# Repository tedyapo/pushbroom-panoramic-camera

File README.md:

# pushbroom-panoramic-camera
Experimental lowres landscape camera

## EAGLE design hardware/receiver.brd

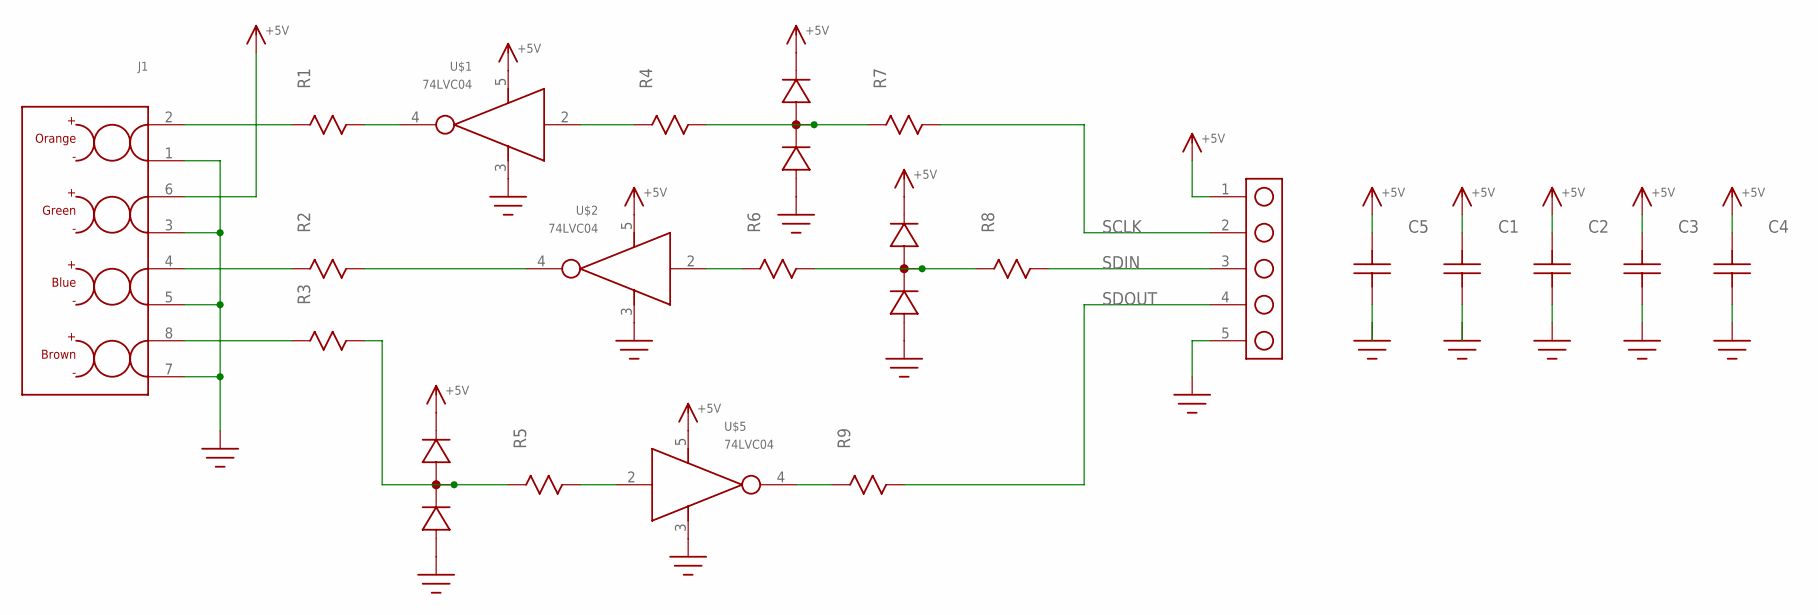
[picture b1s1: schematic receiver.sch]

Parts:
C1, C5: C1206; 1206
C2, C3, C4: C0805; 0805
J1: RJ45; RJ45_KEYSTONE_949
J2: HEADER_5PIN
R1, R2, R3, R4, R5, R6, R7, R8, R9: R0805
U$1, U$2, U$5: 74LVC04; SOT23-5
U$12, U$13, U$14: MMBD7000L; SOT-23

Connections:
+5V: C1.P$2, C2.P$2, C3.P$2, C4.P$2, C5.P$2, J1.6, J2.1, U$1.5 (VCC), U$2.5 (VCC), U$5.5 (VCC), U$12.2 (CATHODE), U$13.2 (CATHODE), U$14.2 (CATHODE)
GND: C1.P$1, C2.P$1, C3.P$1, C4.P$1, C5.P$1, J1.1, J1.3, J1.5, J1.7, J2.5, U$1.3 (GND), U$2.3 (GND), U$5.3 (GND), U$12.1 (ANODE), U$13.1 (ANODE), U$14.1 (ANODE)
unnamed: J1.2, R1.P$1
unnamed: R1.P$2, U$1.4 (OUT)
unnamed: J1.4, R2.P$1
unnamed: R2.P$2, U$2.4 (OUT)
unnamed: J1.8, R3.P$1
unnamed: R3.P$2, R5.P$1, U$14.3 (COMMON)
unnamed: R5.P$2, U$5.2 (IN)
unnamed: R6.P$1, U$2.2 (IN)
unnamed: R4.P$1, U$1.2 (IN)
unnamed: R4.P$2, R7.P$1, U$12.3 (COMMON)
unnamed: R6.P$2, R8.P$1, U$13.3 (COMMON)
unnamed: R9.P$1, U$5.4 (OUT)
SCLK: J2.2, R7.P$2
SDIN: J2.3, R8.P$2
SDOUT: J2.4, R9.P$2

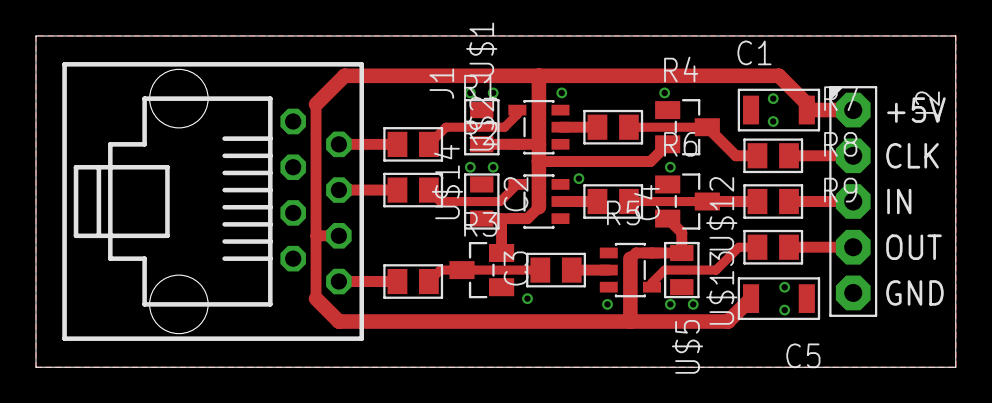
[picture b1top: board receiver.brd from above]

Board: 2 copper layers, 51.1 x 18.4 mm, 22 parts (0 on the bottom side), 17 nets.

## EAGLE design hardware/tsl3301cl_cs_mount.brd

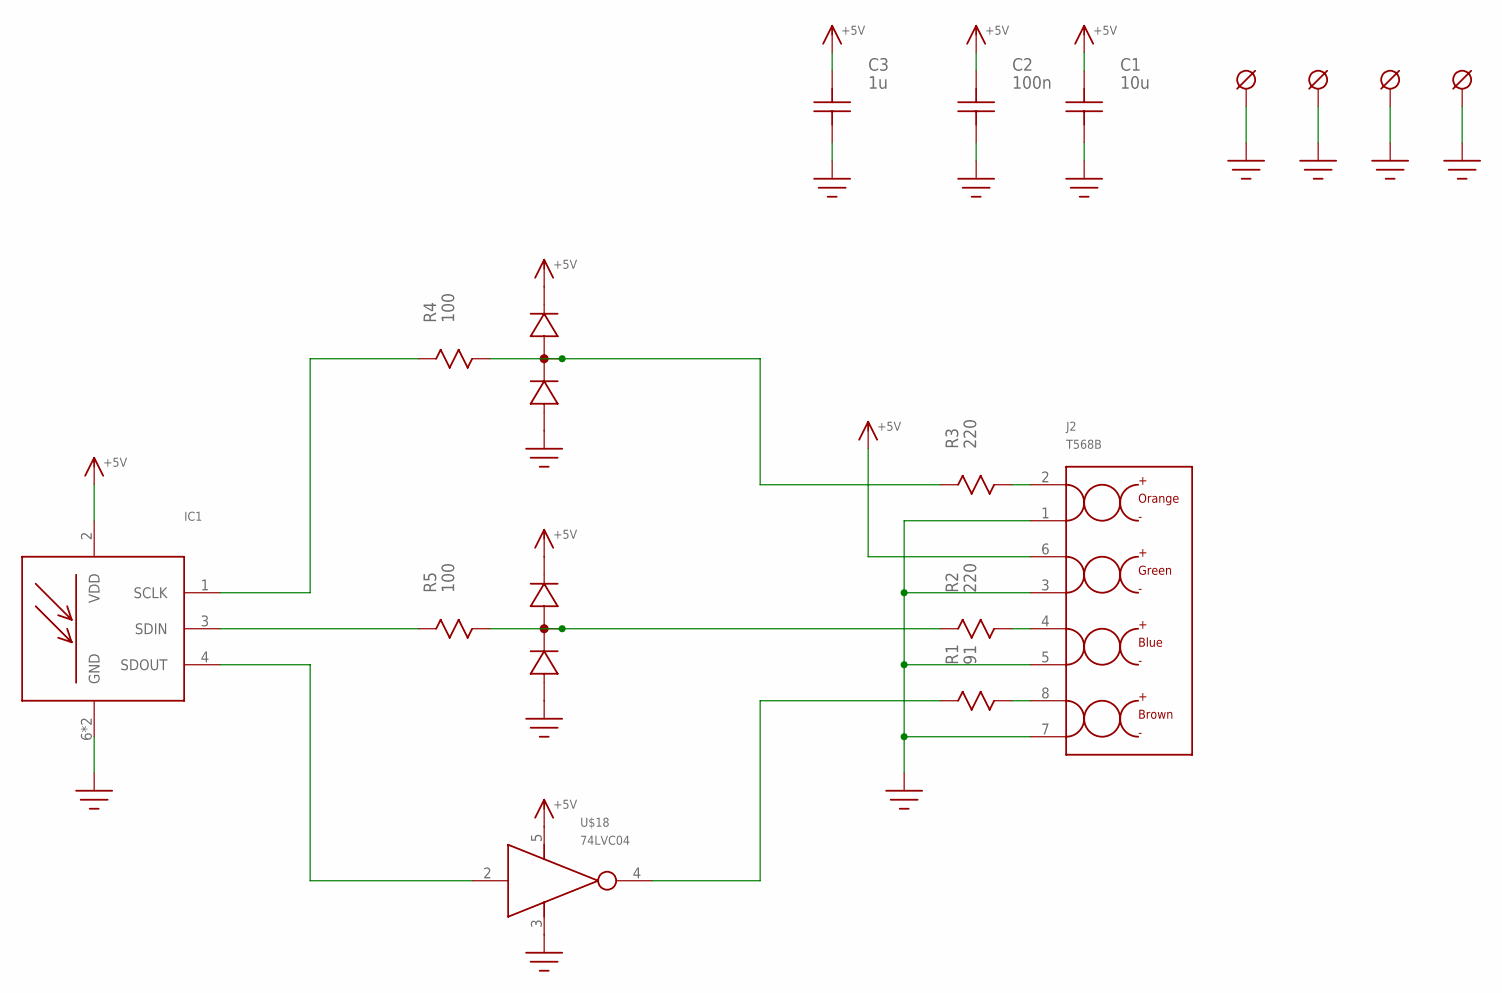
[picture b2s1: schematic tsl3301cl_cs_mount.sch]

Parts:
C1: 10u; 1206
C2: 100n; C0603
C3: 1u; 0805
IC1: TSL3301CL; TSL3301
J2: T568B; RJ45_KEYSTONE_949
R1: 91; R0805
R2, R3: 220; R0805
R4, R5: 100; R0603
U$2, U$3, U$4, U$5: MOUNTING_HOLE; MOUNTING_HOLE_#4
U$18: 74LVC04; SOT23-5
U$21, U$22: MMBD7000L; SOT-23

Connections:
+5V: C1.P$2, C2.P$2, C3.P$2, IC1.2 (VDD), J2.6, U$18.5 (VCC), U$21.2 (CATHODE), U$22.2 (CATHODE)
GND: C1.P$1, C2.P$1, C3.P$1, IC1.6 (GND), IC1.7 (GND), J2.1, J2.3, J2.5, J2.7, U$2.P$1, U$2.P$2, U$2.P$3, U$2.P$4, U$2.P$5, U$2.P$6, U$2.P$7, U$2.P$8, U$2.P$9, U$3.P$1, U$3.P$2, U$3.P$3, U$3.P$4, U$3.P$5, U$3.P$6, U$3.P$7, U$3.P$8, U$3.P$9, U$4.P$1, U$4.P$2, U$4.P$3, U$4.P$4, U$4.P$5, U$4.P$6, U$4.P$7, U$4.P$8, U$4.P$9, U$5.P$1, U$5.P$2, U$5.P$3, U$5.P$4, U$5.P$5, U$5.P$6, U$5.P$7, U$5.P$8, U$5.P$9, U$18.3 (GND), U$21.1 (ANODE), U$22.1 (ANODE)
unnamed: J2.8, R1.P$2
unnamed: J2.2, R3.P$2
unnamed: J2.4, R2.P$2
unnamed: R1.P$1, U$18.4 (OUT)
unnamed: R2.P$1, R5.P$2, U$21.3 (COMMON)
unnamed: R3.P$1, R4.P$2, U$22.3 (COMMON)
unnamed: IC1.1 (SCLK), R4.P$1
unnamed: IC1.3 (SDIN), R5.P$1
unnamed: IC1.4 (SDOUT), U$18.2 (IN)

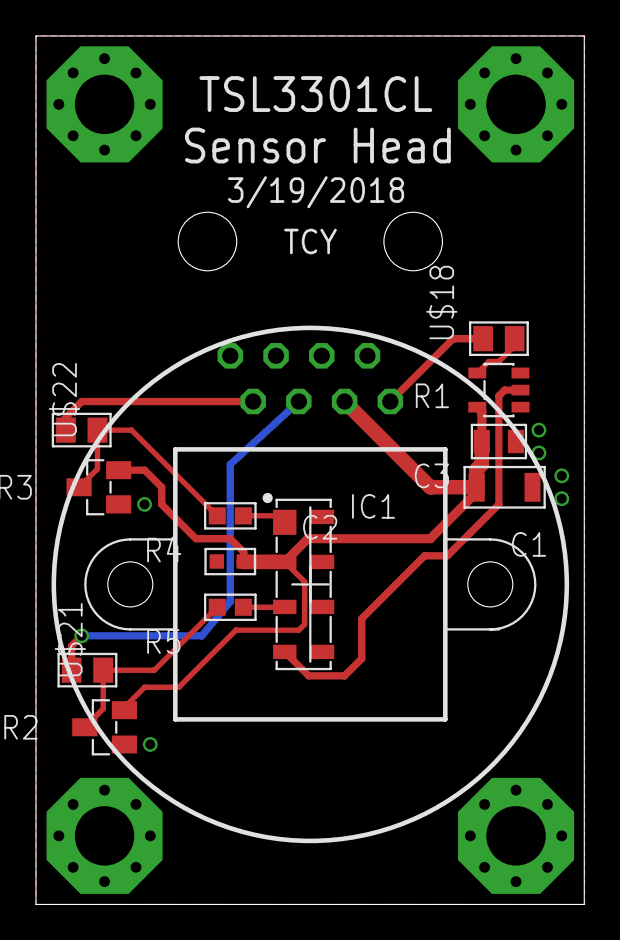
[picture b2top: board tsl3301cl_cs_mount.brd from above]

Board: 2 copper layers, 30.5 x 48.2 mm, 18 parts (1 on the bottom side), 11 nets.

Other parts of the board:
U$1: CS_LENS_MOUNT

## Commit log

2018-03-20 first toy sensor head
2018-03-20 added gerber wrangler script
2018-03-22 added receiver PCB
